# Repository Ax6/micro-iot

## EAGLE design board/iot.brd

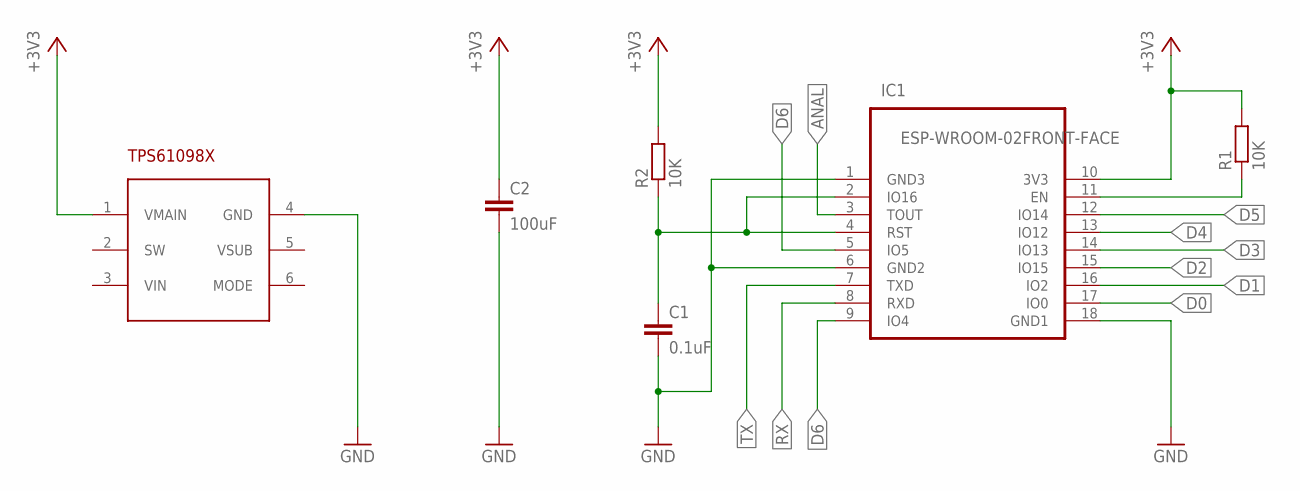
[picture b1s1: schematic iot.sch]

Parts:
C1: 0.1uF; C0603
C2: 100uF; C0805
IC1: ESP-WROOM-02FRONT-FACE; FRONT-FACE
R1, R2: 10K; R0603
U$1: TPS810986; S-PWSON-N6

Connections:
+3V3: C2.1, IC1.10 (3V3), R1.2, R2.2, U$1.1 (VMAIN)
ANAL: IC1.3 (TOUT)
D0: IC1.17 (IO0)
D1: IC1.16 (IO2)
D2: IC1.15 (IO15)
D3: IC1.14 (IO13)
D4: IC1.13 (IO12)
D5: IC1.12 (IO14)
D6: IC1.5 (IO5), IC1.9 (IO4)
EN: IC1.11 (EN), R1.1
GND: C1.2, C2.2, IC1.1 (GND3), IC1.6 (GND2), IC1.18 (GND1), U$1.4 (GND)
unnamed: C1.1, IC1.2 (IO16), IC1.4 (RST), R2.1
RX: IC1.8 (RXD)
TX: IC1.7 (TXD)

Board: 2 copper layers, 6 parts (1 on the bottom side), 5 nets, no tracks yet.
